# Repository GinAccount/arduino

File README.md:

Arduino Community
=================

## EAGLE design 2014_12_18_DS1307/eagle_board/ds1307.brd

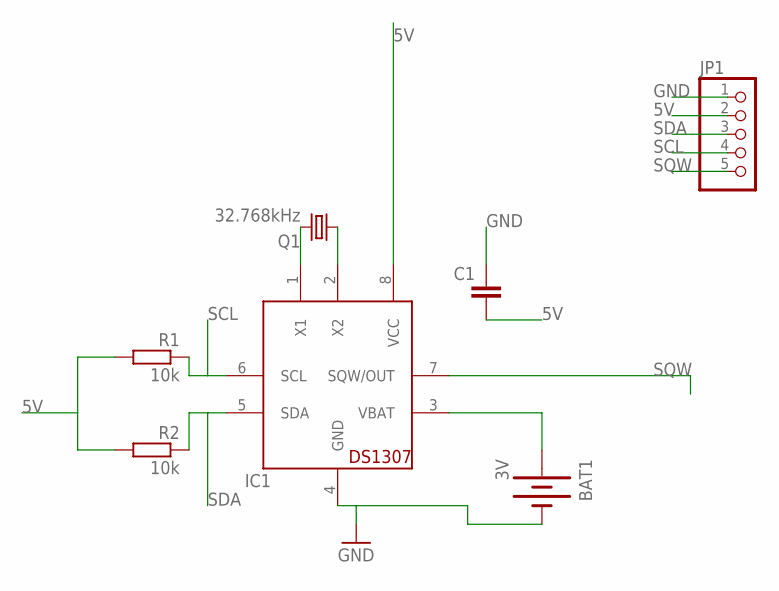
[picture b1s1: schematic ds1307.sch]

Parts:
BAT1: 3V; BATTCOM_20MM_PTH
C1: C-EUC1206; C1206
IC1: DS1307; DIL08
JP1: PINHD-1X5; 1X05
Q1: 32.768kHz; TC38H
R1, R2: 10k; R1206

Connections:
5V: C1.2, IC1.8 (VCC), JP1.2, R1.2, R2.2
GND: BAT1.2 (-), C1.1, IC1.4 (GND), JP1.1
unnamed: IC1.2 (X2), Q1.1
unnamed: IC1.1 (X1), Q1.2
unnamed: BAT1.1 (+), IC1.3 (VBAT)
SCL: IC1.6 (SCL), JP1.4, R1.1
SDA: IC1.5 (SDA), JP1.3, R2.1
SQW: IC1.7 (SQW/OUT), JP1.5

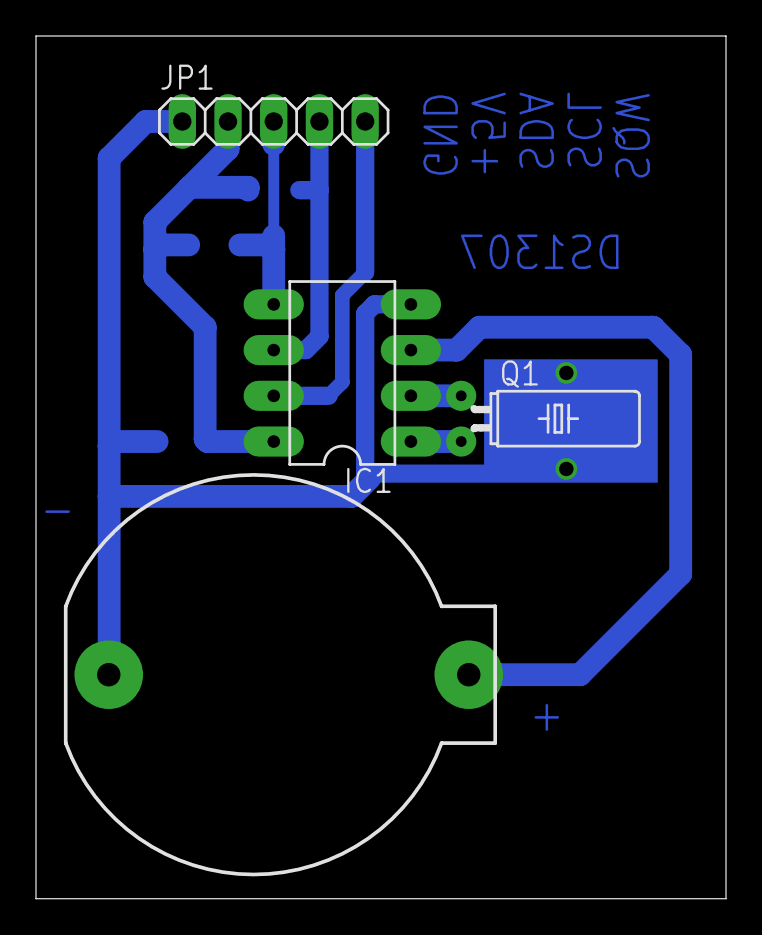
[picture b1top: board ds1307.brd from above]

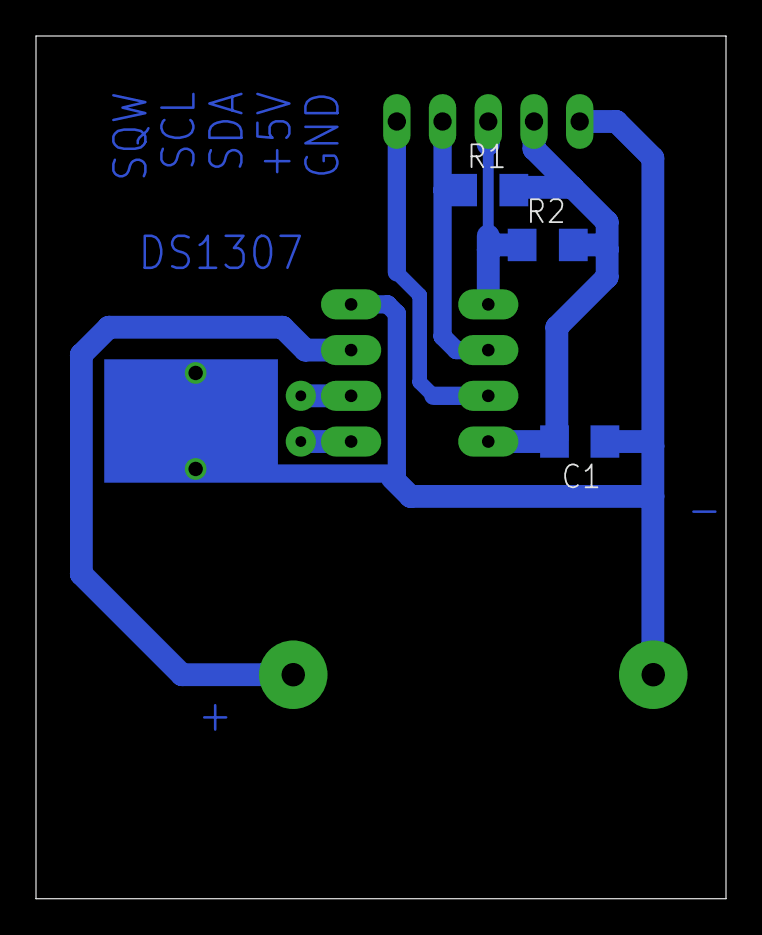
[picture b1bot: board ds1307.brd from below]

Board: 2 copper layers, 38.3 x 47.9 mm, 7 parts (3 on the bottom side), 8 nets.

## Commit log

2014-11-15 hello world
2014-11-15 test
2014-12-06 BMP180
2014-12-06 refactor
2014-12-18 Added DS1307 Real Time Clock details
2014-12-25 DHT11 sensor Hello World script

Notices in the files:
parts and their libraries:
SparkFun-FreqCtrl: Licensing: Creative Commons ShareAlike 4.0 International - https://creativecommons.org/licenses/by-sa/4.0
